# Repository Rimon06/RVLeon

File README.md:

# RVLeon
Trabajo final de grado

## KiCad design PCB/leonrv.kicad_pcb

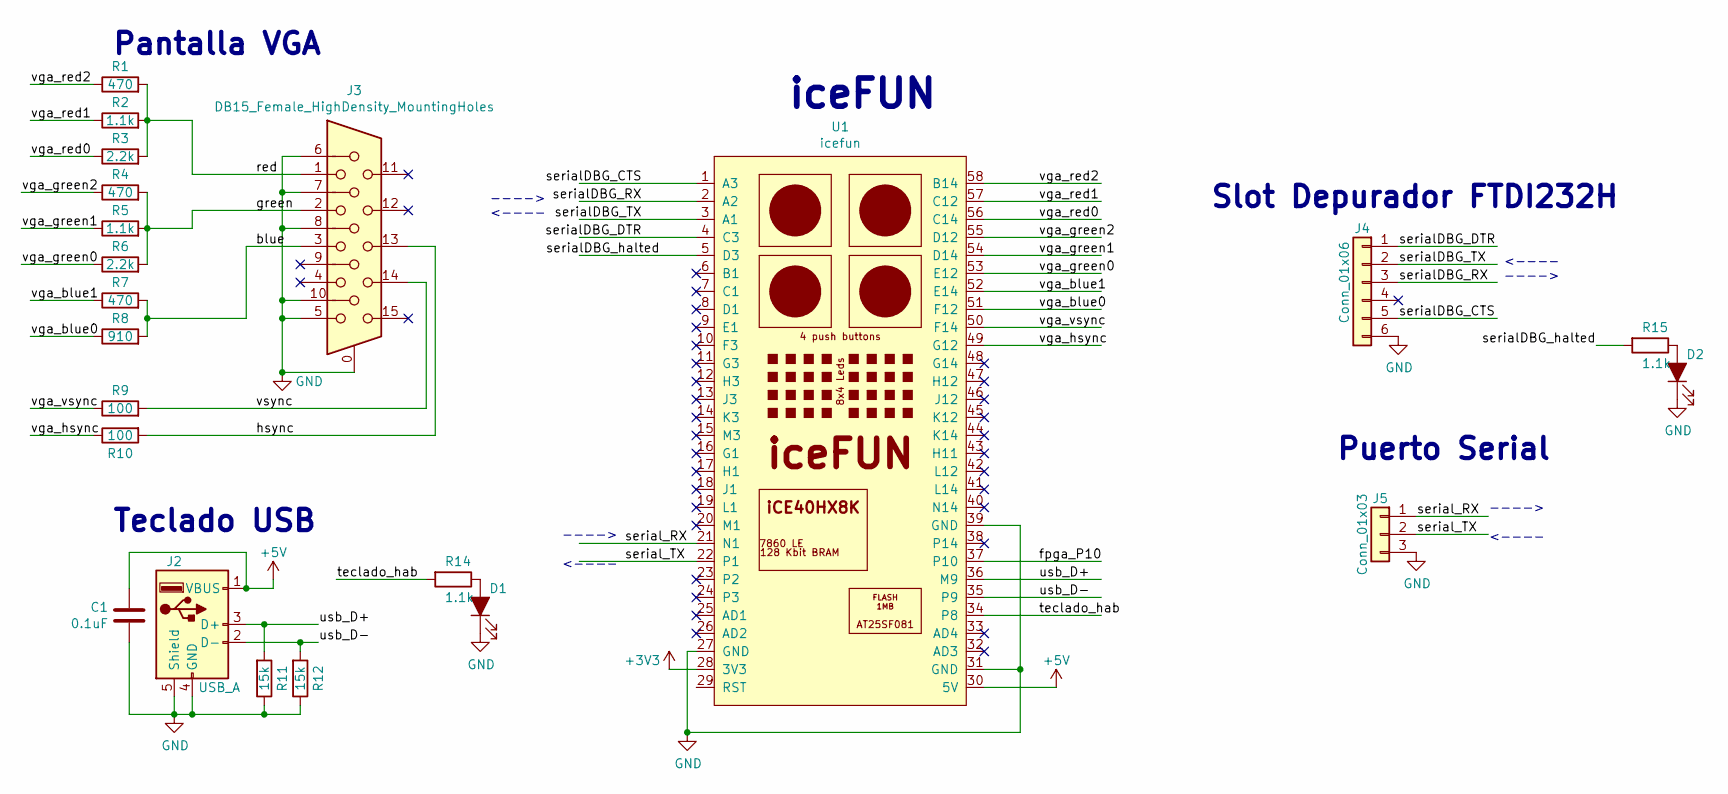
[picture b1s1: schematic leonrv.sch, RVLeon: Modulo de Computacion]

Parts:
C1: 0.1uF; CP_Radial_D5.0mm_P2.50mm
D1, D2: LED_ALT; LED_D5.0mm
J2: USB_A; USB_A_Female_UE27AC54100
J3: DB15_Female_HighDensity_MountingHoles; DSUB-15-HD_Female_Horizontal_P2.29x1.98mm_EdgePinOffset3.03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
J4: Conn_01x06; PinSocket_1x06_P2.54mm_Vertical
J5: Conn_01x03; PinSocket_1x03_P2.54mm_Vertical
R1, R4, R7: 470; R_Axial_DIN0411_L9.9mm_D3.6mm_P12.70mm_Horizontal
R2, R5, R14, R15: 1.1k; R_Axial_DIN0411_L9.9mm_D3.6mm_P12.70mm_Horizontal
R3, R6: 2.2k; R_Axial_DIN0411_L9.9mm_D3.6mm_P12.70mm_Horizontal
R8: 910; R_Axial_DIN0411_L9.9mm_D3.6mm_P12.70mm_Horizontal
R9, R10: 100; R_Axial_DIN0411_L9.9mm_D3.6mm_P12.70mm_Horizontal
R11, R12: 15k; R_Axial_DIN0411_L9.9mm_D3.6mm_P12.70mm_Horizontal
U1: icefun; icefun-DIP

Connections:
+3V3: U1.28 (3V3)
+5V: C1.2, J2.1 (VBUS), U1.30 (5V)
/blue: J3.3, R7.2, R8.2
/fpga_P10: U1.37 (P10)
/green: J3.2, R4.2, R5.2, R6.2
/hsync: J3.13, R10.2
/red: J3.1, R1.2, R2.2, R3.2
/serialDBG_CTS: J4.5, U1.1 (A3)
/serialDBG_DTR: J4.1, U1.4 (C3)
/serialDBG_RX: J4.3, U1.2 (A2)
/serialDBG_TX: J4.2, U1.3 (A1)
/serialDBG_halted: R15.2, U1.5 (D3)
/serial_RX: J5.1, U1.21 (N1)
/serial_TX: J5.2, U1.22 (P1)
/teclado_hab: R14.2, U1.34 (P8)
/usb_D+: J2.3 (D+), R11.2, U1.36 (M9)
/usb_D-: J2.2 (D-), R12.2, U1.35 (P9)
/vga_blue0: R8.1, U1.51 (F12)
/vga_blue1: R7.1, U1.52 (E14)
/vga_green0: R6.1, U1.53 (E12)
/vga_green1: R5.1, U1.54 (D14)
/vga_green2: R4.1, U1.55 (D12)
/vga_hsync: R10.1, U1.49 (G12)
/vga_red0: R3.1, U1.56 (C14)
/vga_red1: R2.1, U1.57 (C12)
/vga_red2: R1.1, U1.58 (B14)
/vga_vsync: R9.1, U1.50 (F14)
/vsync: J3.14, R9.2
GND: C1.1, D1.1 (K), D2.1 (K), J2.4 (GND), J2.5 (Shield), J3.0, J3.5, J3.6, J3.7, J3.8, J3.10, J4.6, J5.3, R11.1, R12.1, U1.27 (GND), U1.31 (GND), U1.39 (GND)
unnamed: D1.2 (A), R14.1
unnamed: D2.2 (A), R15.1

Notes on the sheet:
iceFUN
Teclado USB
Pantalla VGA
Slot Depurador FTDI232H
Puerto Serial
----> <----
----> <----
<---- ---->

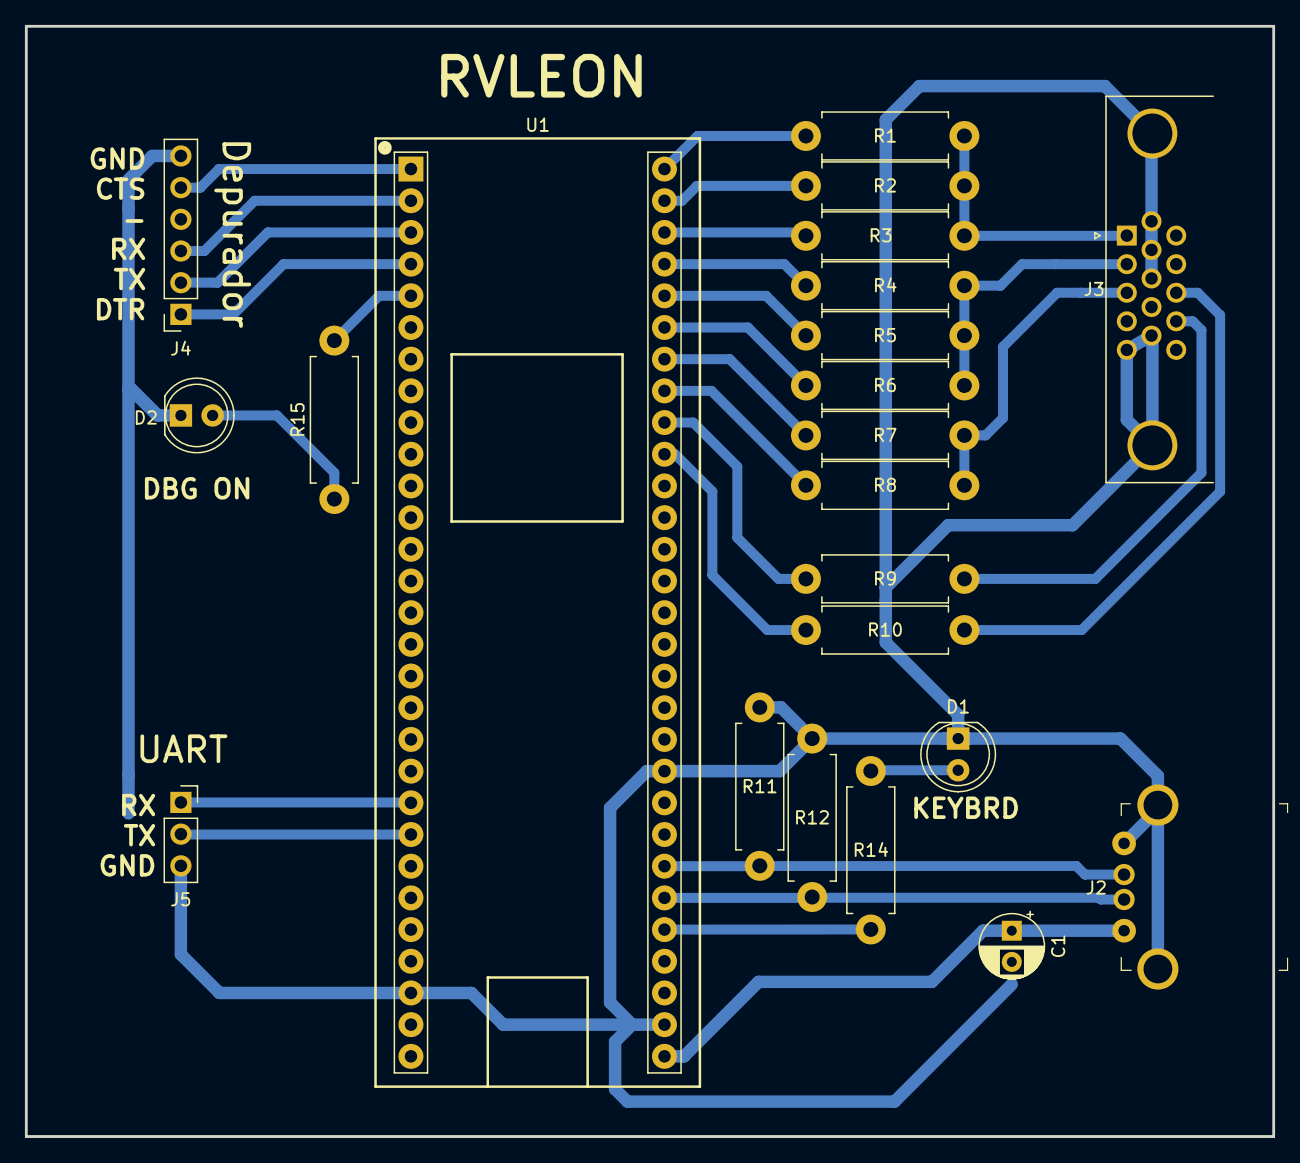
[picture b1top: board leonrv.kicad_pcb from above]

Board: 2 copper layers, 100.0 x 89.0 mm, 22 parts (0 on the bottom side), 29 nets.

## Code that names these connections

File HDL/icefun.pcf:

set_io --warn-no-port led[0] 	C10
set_io --warn-no-port led[1]	A10
set_io --warn-no-port led[2]	D7
set_io --warn-no-port led[3]	D6
set_io --warn-no-port led[4] 	A7
set_io --warn-no-port led[5] 	C7
set_io --warn-no-port led[6] 	A4
set_io --warn-no-port led[7] 	C4

set_io --warn-no-port lcol[3]	A12
set_io --warn-no-port lcol[2]	D10
set_io --warn-no-port lcol[1]	A6
set_io --warn-no-port lcol[0]	C5

# set_io --warn-no-port spkp  	M12
# set_io --warn-no-port spkm  	M6

set_io --warn-no-port key[0]	C11
set_io --warn-no-port key[1]	C6
set_io --warn-no-port key[2]	A11
set_io --warn-no-port key[3]	A5

set_io --warn-no-port flash_cs_n P13
set_io --warn-no-port flash_mosi M11
set_io --warn-no-port flash_miso P11	
set_io --warn-no-port flash_sclk P12

set_io --warn-no-port clk12MHz	P7

set_io --warn-no-port RXD		N1
set_io --warn-no-port TXD		P1

set_io --warn-no-port dbg_RXD	A2
set_io --warn-no-port dbg_TXD	A1
set_io --warn-no-port dbg_ON    D3

set_io --warn-no-port teclado_hab	P8
set_io usbdp		M9
set_io usbdm	 	P9


set_io --warn-no-port vga_red[2]    B14
set_io --warn-no-port vga_red[1]    C12
set_io --warn-no-port vga_red[0]    C14
set_io --warn-no-port vga_green[2]  D12
set_io --warn-no-port vga_green[1]  D14
set_io --warn-no-port vga_green[0]  E12
set_io --warn-no-port vga_blue[1]   E14
set_io --warn-no-port vga_blue[0]   F12

set_io --warn-no-port vga_hsync     G12
set_io --warn-no-port vga_vsync     F14

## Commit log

2024-03-22 Pruebas de Software
2024-03-22 Depurador
2024-03-22 Archivo binario
